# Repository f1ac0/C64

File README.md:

# C64
I bought my fisrt C64. It was listed as "Untested", and of course it was faulty (12v fuse in PSU, 6569 VIC-II that I replaced with a 8565, RAM U10 replaced with a 41256 and 7406 U8 with dead output to IEC port).

While repairing it, I learned about the components inside the C64, their signals and common faults. I bookmarked open-source alternatives and useful expansions : below is a list of the projects I found interesting.

In this repository I share the boards I created or modified for my own needs (for example to use the parts I have in stock, to add features, or because I like my own routing). At the time of writing, some are still untested. 

# Disclaimer and Acknowledgements
This is a hobbyist project, it comes with no warranty and no support. Also remember that the Commodore machines are about 40 years old and may fail because of such hardware expansions.

I publish my work under the CC-BY-NC-SA license, unless stated otherwise. Thanks to everyone who share their knowledge and creations.

# Cartridge
Simple cartridges :
- https://github.com/bwack/Versa64Cart
- https://github.com/SukkoPera/OpenC64Cart
- https://github.com/SukkoPera/OpenC64Cart16K
- https://github.com/SukkoPera/OpenC64KernalCart

Diagnostic :
- https://github.com/svenpetersen1965/Diag64cart
- https://github.com/svenpetersen1965/C64-Diagnostic-Rev.-586220-Harness

Advanced cartridges :
- https://github.com/KimJorgensen/KungFuFlash
- https://github.com/Sgw32/KungFuFlashGD32
- https://github.com/frntc/RAD
- https://github.com/crystalct/MagicDesk2
- https://github.com/msolajic/c64-uni-cart

# CIA

# CPU
- https://github.com/monotech/MOS_CPU_Replacer

# Drive
- https://cbm-pi1541.firebaseapp.com/
- https://github.com/pi1541/Pi1541
- https://github.com/hackup/Pi1541io
- https://github.com/tebl/C64-Pi1541-Module
- https://github.com/Beaupre-Circuit-Design/c64-Pi1541

# Modulator
- https://github.com/c0pperdragon/C64-Video-Enhancement/tree/master/analog_only
- https://github.com/pmandes/C64-RF-Modulator
- https://github.com/tebl/C64-Modulator-Replacement
- https://github.com/mbarszcz-pcb/c64-rf-modulator-replacement

# PLA
- https://github.com/1c3d1v3r/neatPLA
- https://github.com/desaster/c64-dodgypla
- https://www.freepascal.org/~daniel/c64pla/

# RAM

# ROM
- https://github.com/SukkoPera/Open2327RomAdapter
- https://www.hackup.net/2022/05/the-kernal-quattro-a-2364-rom-replacement/

# SID
- http://tolaemon.com/nss/
- https://github.com/jsanpe/SwinsidNeat
- https://github.com/dmantione/swinsid

# Tape
- https://github.com/sweetlilmre/tapuino
- http://sweetlilmre.blogspot.com/2015/03/building-tapuino-r2.html
- https://github.com/sweetlilmre/TapuinoNext

# VIC2
- https://github.com/Jartza/8565_adapter

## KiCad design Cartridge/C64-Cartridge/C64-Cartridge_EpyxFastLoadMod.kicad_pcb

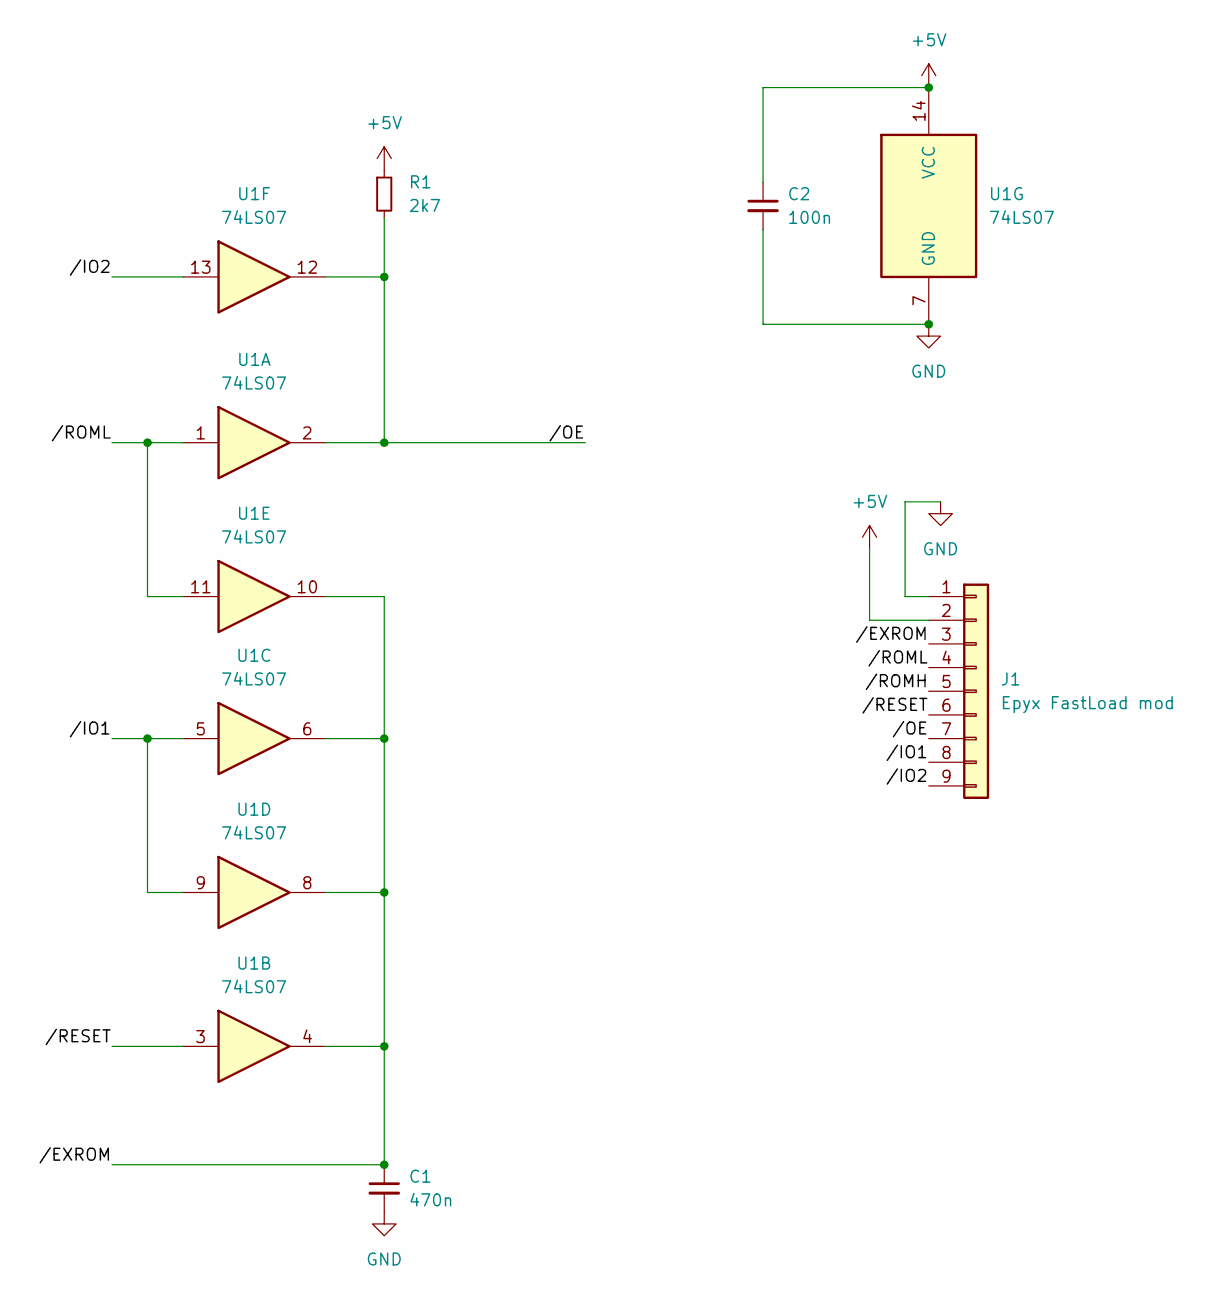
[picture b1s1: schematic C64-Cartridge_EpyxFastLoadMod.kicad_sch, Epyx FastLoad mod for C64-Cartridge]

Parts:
C1: 470n; C_0805_2012Metric
C2: 100n; C_0805_2012Metric
J1: Epyx FastLoad mod; PinHeader_1x09_P1.27mm_Vertical
R1: 2k7; R_0805_2012Metric
U1: 74LS07; SOIC-14_3.9x8.7mm_P1.27mm

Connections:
+5V: C2.1, J1.2, R1.1, U1.14 (VCC)
//EXROM: C1.1, J1.3, U1.4, U1.6, U1.8, U1.10
//IO1: J1.8, U1.5, U1.9
//IO2: J1.9, U1.13
//OE: J1.7, R1.2, U1.2, U1.12
//RESET: J1.6, U1.3
//ROMH: J1.5
//ROML: J1.4, U1.1, U1.11
GND: C1.2, C2.2, J1.1, U1.7 (GND)

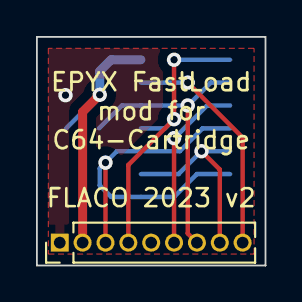
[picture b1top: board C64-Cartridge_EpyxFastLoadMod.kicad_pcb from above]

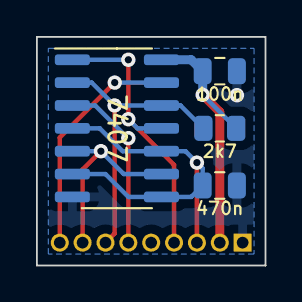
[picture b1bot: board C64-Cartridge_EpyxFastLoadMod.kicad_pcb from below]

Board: 2 copper layers, 12.7 x 12.7 mm, 5 parts (4 on the bottom side), 8 nets.

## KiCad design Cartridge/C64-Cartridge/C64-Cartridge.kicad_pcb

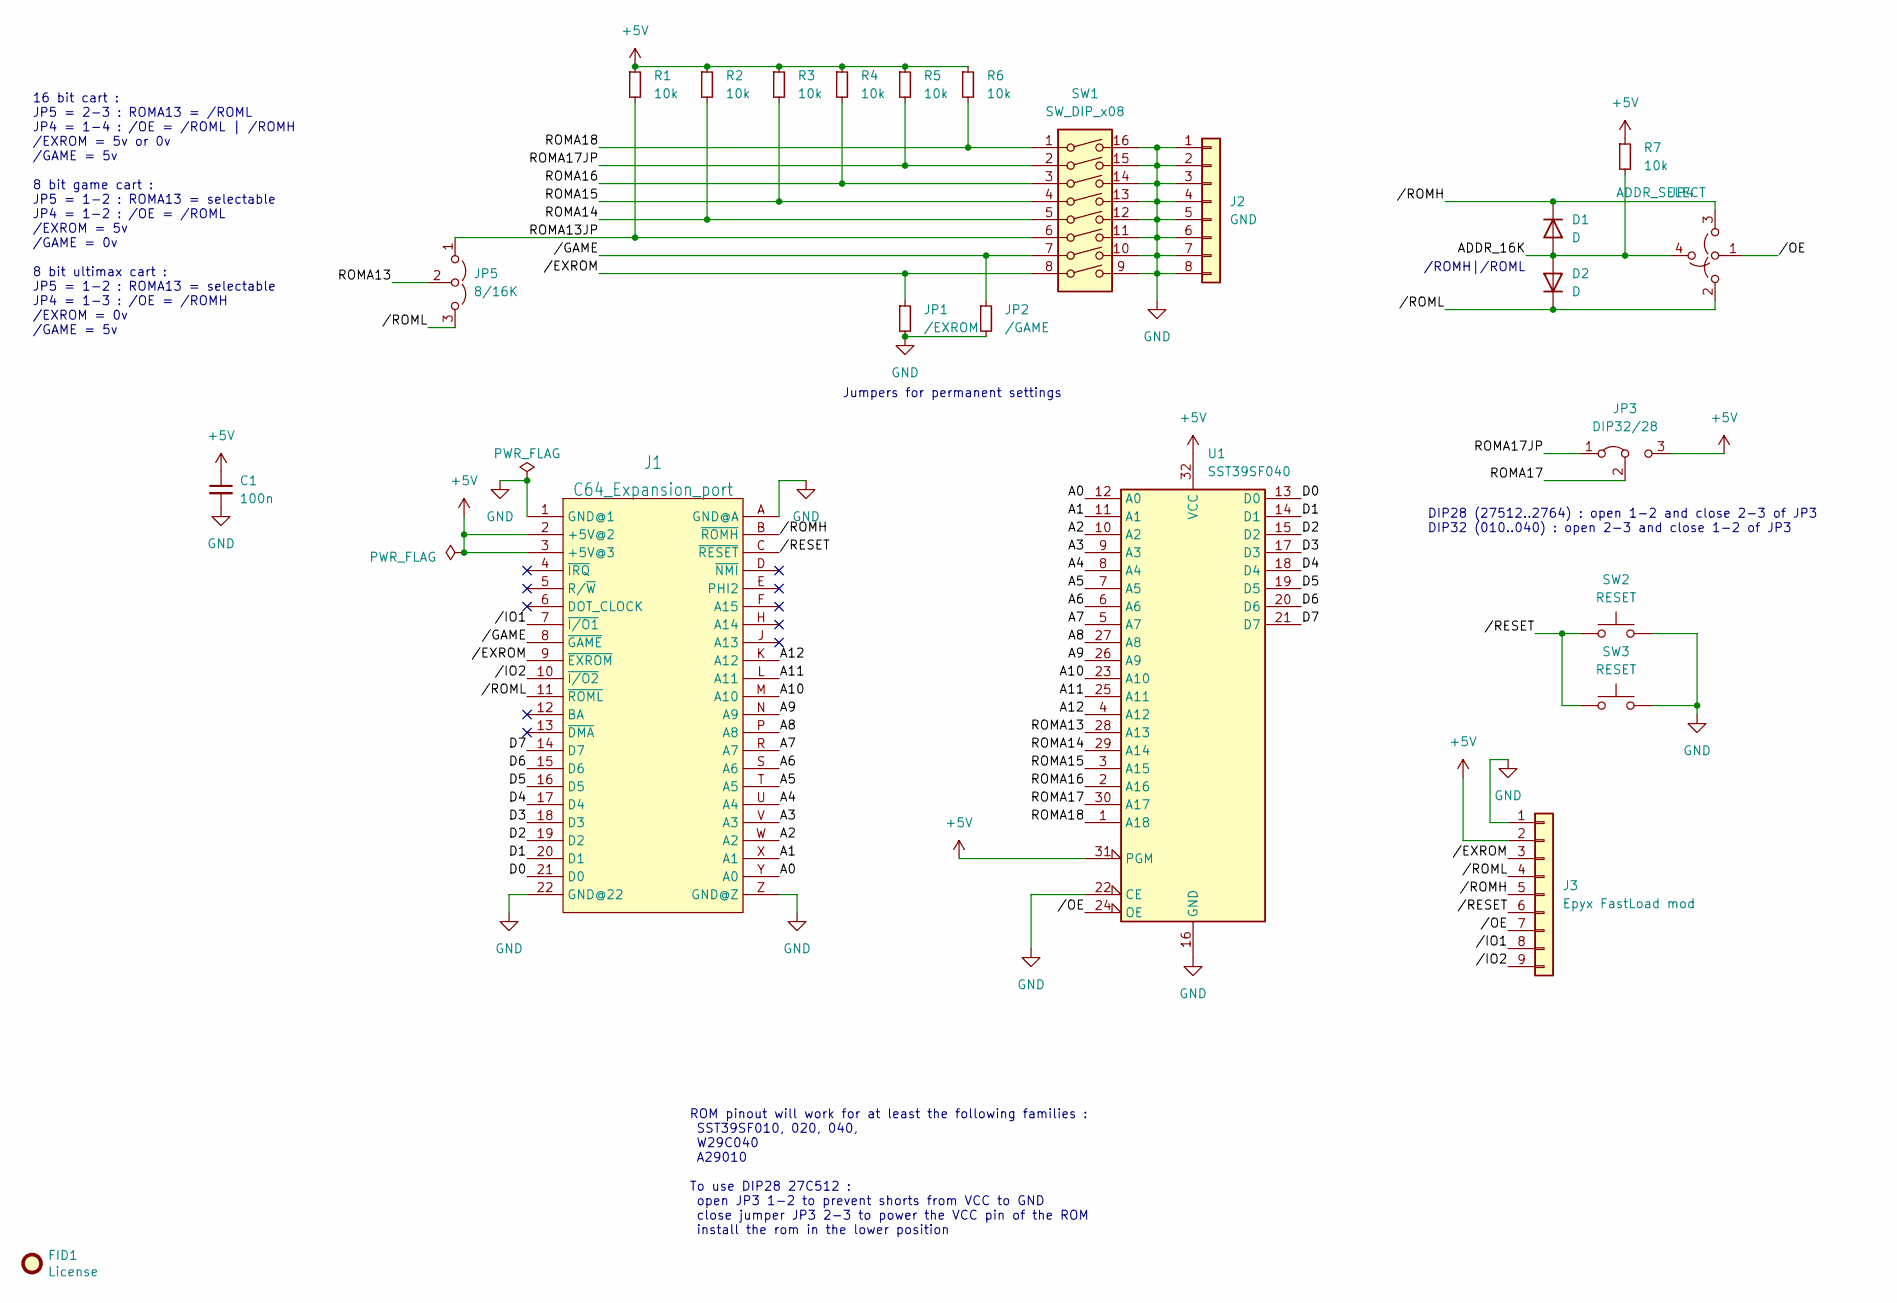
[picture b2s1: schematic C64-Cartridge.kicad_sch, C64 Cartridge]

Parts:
C1: 100n; C_0805_2012Metric
D1, D2: D; D_0805_2012Metric
FID1: License; CC_BY_NC_SA_square_silkscreen
J1: C64_Expansion_port; C64_Expansion_2x22_P2.54mm
J2: GND; PinHeader_1x08_P2.54mm_Vertical
J3: Epyx FastLoad mod; PinHeader_1x09_P1.27mm_Vertical
JP1: /EXROM; SolderJumper-2_P1.3mm_Open_RoundedPad1.0x1.5mm
JP2: /GAME; SolderJumper-2_P1.3mm_Open_RoundedPad1.0x1.5mm
JP3: DIP32/28; SolderJumper-3_P1.3mm_Open_RoundedPad1.0x1.5mm
JP4: ADDR_SELECT; Jumper_4_SPTT_P2.54mm_Vertical
JP5: 8/16K; Jumper_3_SPDT_P2.54mm_Vertical
R1, R2, R3, R4, R5, R6, R7: 10k; R_0805_2012Metric
SW1: SW_DIP_x08; SW_DIP_SPSTx08_Slide_9.78x22.5mm_W7.62mm_P2.54mm
SW2: RESET; SW_SPST_FSMSM
SW3: RESET; SW_PUSH_6mm
U1: SST39SF040; DIP-32_W15.24mm

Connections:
+5V: C1.1, J1.2 (+5V@2), J1.3 (+5V@3), J3.2, JP3.3 (B), R1.1, R2.1, R3.1, R4.1, R5.1, R6.1, R7.1, U1.31 (PGM), U1.32 (VCC)
/A0: J1.Y (A0), U1.12 (A0)
/A1: J1.X (A1), U1.11 (A1)
/A2: J1.W (A2), U1.10 (A2)
/A3: J1.V (A3), U1.9 (A3)
/A4: J1.U (A4), U1.8 (A4)
/A5: J1.T (A5), U1.7 (A5)
/A6: J1.S (A6), U1.6 (A6)
/A7: J1.R (A7), U1.5 (A7)
/A8: J1.P (A8), U1.27 (A8)
/A9: J1.N (A9), U1.26 (A9)
/A10: J1.M (A10), U1.23 (A10)
/A11: J1.L (A11), U1.25 (A11)
/A12: J1.K (A12), U1.4 (A12)
/ADDR_16K: D1.2 (A), D2.2 (A), JP4.4 (D), R7.2
/D0: J1.21 (D0), U1.13 (D0)
/D1: J1.20 (D1), U1.14 (D1)
/D2: J1.19 (D2), U1.15 (D2)
/D3: J1.18 (D3), U1.17 (D3)
/D4: J1.17 (D4), U1.18 (D4)
/D5: J1.16 (D5), U1.19 (D5)
/D6: J1.15 (D6), U1.20 (D6)
/D7: J1.14 (D7), U1.21 (D7)
/ROMA13: JP5.2 (C), U1.28 (A13)
/ROMA13JP: JP5.1 (A), R1.2, SW1.6
/ROMA14: R2.2, SW1.5, U1.29 (A14)
/ROMA15: R3.2, SW1.4, U1.3 (A15)
/ROMA16: R4.2, SW1.3, U1.2 (A16)
/ROMA17: JP3.2 (C), U1.30 (A17)
/ROMA17JP: JP3.1 (A), R5.2, SW1.2
/ROMA18: R6.2, SW1.1, U1.1 (A18)
//EXROM: J1.9 (~EXROM), J3.3, JP1.1, SW1.8
//GAME: J1.8 (~GAME), JP2.1, SW1.7
//IO1: J1.7 (~I/O1), J3.8
//IO2: J1.10 (~I/O2), J3.9
//OE: J3.7, JP4.1 (A), U1.24 (OE)
//RESET: J1.C (~RESET), J3.6, SW2.1, SW3.1
//ROMH: D1.1 (K), J1.B (~ROMH), J3.5, JP4.3 (B)
//ROML: D2.1 (K), J1.11 (~ROML), J3.4, JP4.2 (B), JP5.3 (B)
GND: C1.2, J1.1 (GND@1), J1.22 (GND@22), J1.A (GND@A), J1.Z (GND@Z), J2.1, J2.2, J2.3, J2.4, J2.5, J2.6, J2.7, J2.8, J3.1, JP1.2, JP2.2, SW1.9, SW1.10, SW1.11, SW1.12, SW1.13, SW1.14, SW1.15, SW1.16, SW2.2, SW3.2, U1.16 (GND), U1.22 (CE)

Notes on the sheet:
Jumpers for permanent settings
/ROMH|/ROML
16 bit cart : JP5 = 2-3 : ROMA13 = /ROML JP4 = 1-4 : /OE = /ROML | /ROMH /EXROM = 5v or 0v /GAME = 5v 8 bit game cart : JP5 = 1-2 : ROMA13 = selectable JP4 = 1-2 : /OE = /ROML /EXROM = 5v /GAME = 0v 8 bit ultimax cart : JP5 = 1-2 : ROMA13 = selectable JP4 = 1-3 : /OE = /ROMH /EXROM = 0v /GAME = 5v
ROM pinout will work for at least the following families : SST39SF010, 020, 040, W29C040 A29010 To use DIP28 27C512 : open JP3 1-2 to prevent shorts from VCC to GND close jumper JP3 2-3 to power the VCC pin of the ROM install the rom in the lower position
DIP28 (27512..2764) : open 1-2 and close 2-3 of JP3 DIP32 (010..040) : open 2-3 and close 1-2 of JP3

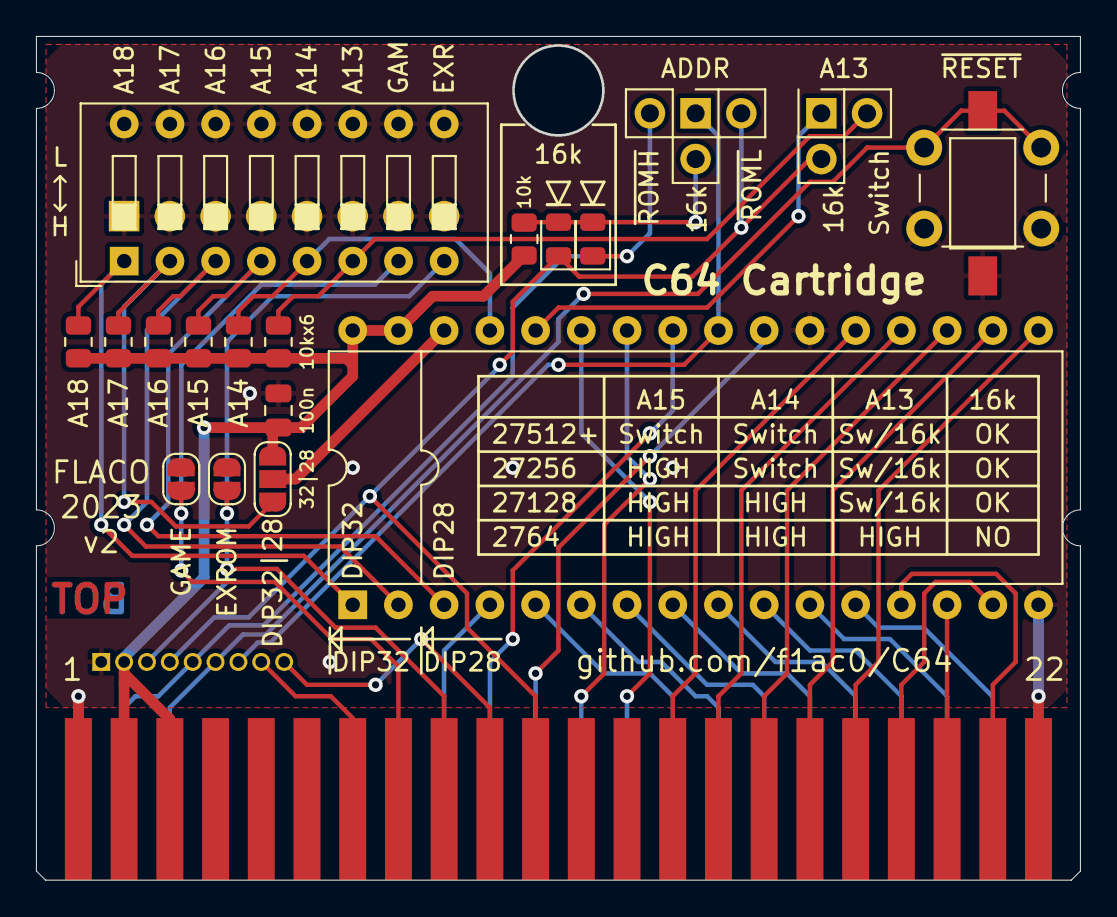
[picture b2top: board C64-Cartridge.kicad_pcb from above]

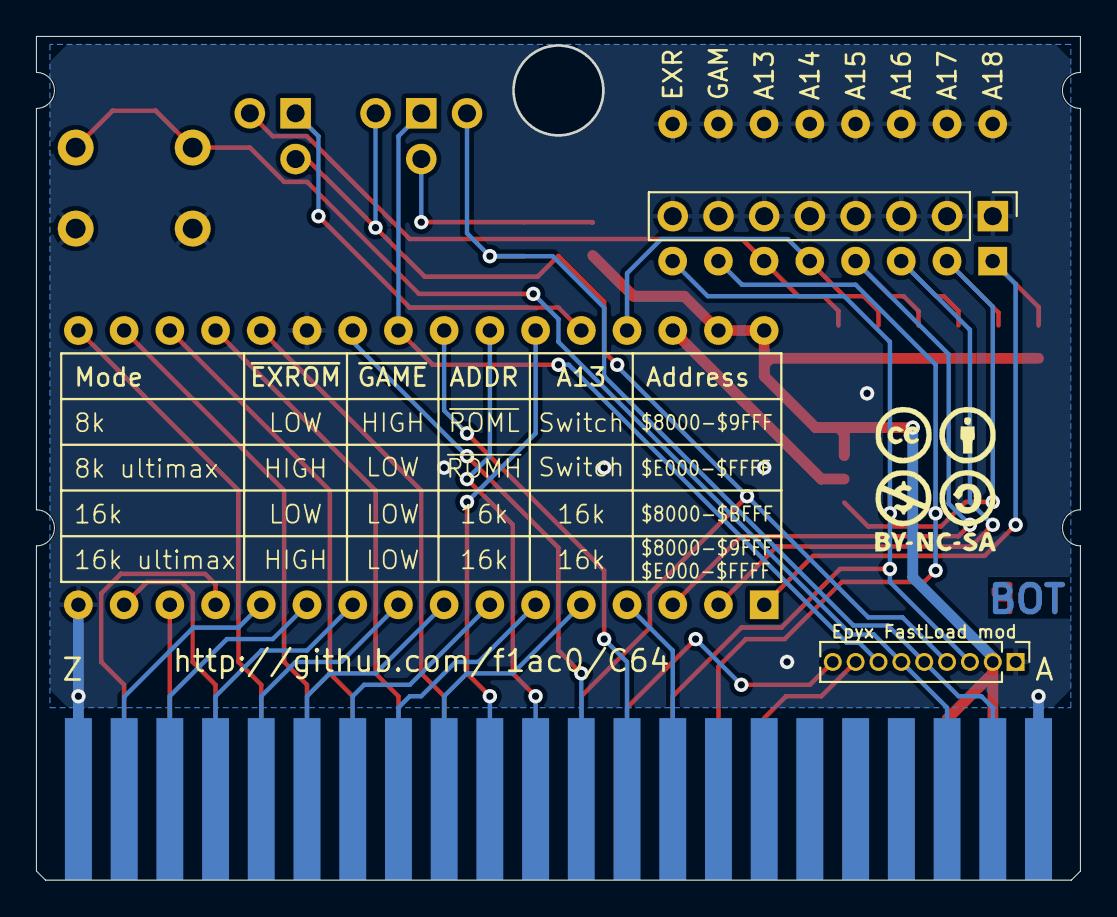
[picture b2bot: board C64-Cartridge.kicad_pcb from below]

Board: 2 copper layers, 57.9 x 46.8 mm, 23 parts (3 on the bottom side), 40 nets.

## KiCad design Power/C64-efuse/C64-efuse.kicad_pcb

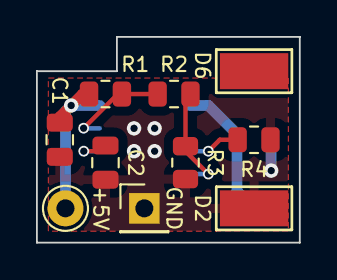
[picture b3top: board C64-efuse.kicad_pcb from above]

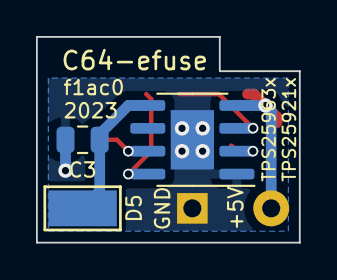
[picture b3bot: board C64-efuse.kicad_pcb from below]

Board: 2 copper layers, 14.6 x 11.4 mm, 13 parts (3 on the bottom side), 7 nets.

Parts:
C1, C3: 0.1-1uF; C_0805_2012Metric
C2: C_dVdt; C_0805_2012Metric
H1: Pin 6 mount; TestPoint_Keystone_5019_Minature
J1: +5V; Pin_D1.0mm_L10.0mm
J2: GND; PinHeader_1x01_P2.54mm_Vertical
J3: Pin 5; TestPoint_Keystone_5019_Minature
J4: Pin 2; TestPoint_Keystone_5019_Minature
R1, R2, R3: R_Small; R_0805_2012Metric
R4: R_ILIM; R_0805_2012Metric
U2: TPS259630; SOIC-8-1EP_3.9x4.9mm_P1.27mm_EP2.41x3.3mm

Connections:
+5F: C3.1, J3.1, U2.5 (OUT)
+5V: C1.1, J1.1, R1.1, U2.4 (VIN)
GND: C1.2, C2.2, C3.2, J2.1, J4.1, R3.2, R4.2, U2.1 (GND), U2.9 (GND)
unnamed: R1.2, R2.1, U2.3 (EN/UVLO)
unnamed: R4.1, U2.7 (ILIM)
unnamed: R2.2, R3.1, U2.8 (OVLO/OVCSEL)
unnamed: C2.1, U2.2 (dV/dT)

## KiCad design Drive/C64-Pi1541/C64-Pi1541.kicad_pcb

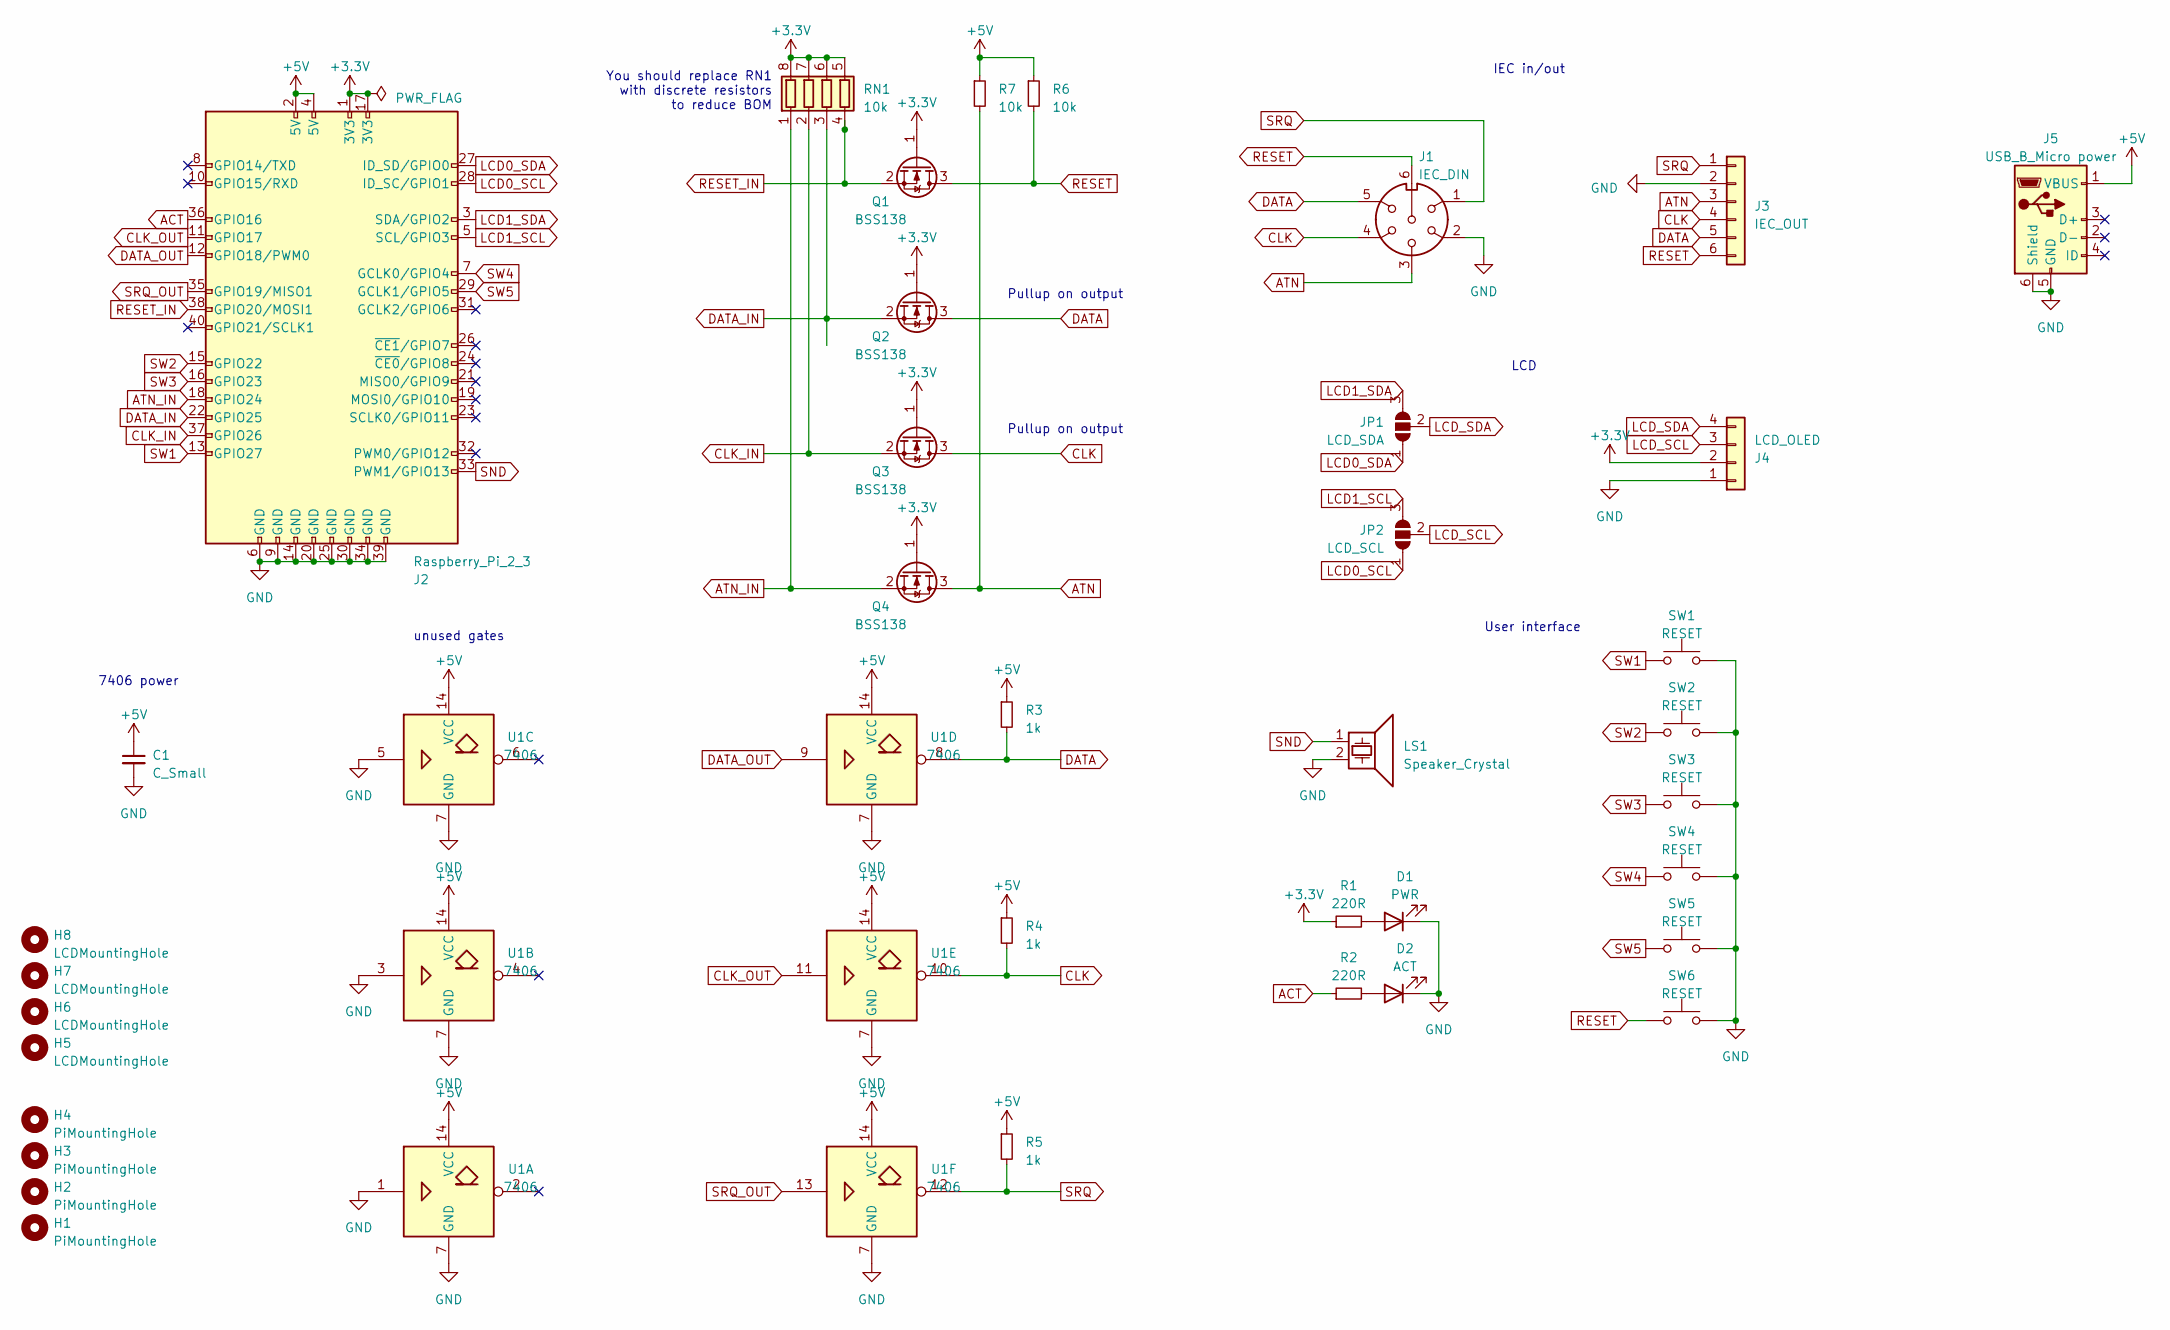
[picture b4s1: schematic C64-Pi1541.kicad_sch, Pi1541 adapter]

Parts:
C1: C_Small; C_0805_2012Metric
D1: PWR; D_0805_2012Metric
D2: ACT; D_0805_2012Metric
H1, H2, H3, H4: PiMountingHole; MountingHole_2.5mm
H5, H6, H7, H8: LCDMountingHole; MountingHole_2.5mm
J1: IEC_DIN; DIN-6-Variable
J2: Raspberry_Pi_2_3; PinSocket_2x20_P2.54mm_Vertical
J3: IEC_OUT; PinHeader_1x06_P2.54mm_Vertical
J4: LCD_OLED; PinSocket_1x04_P2.54mm_Vertical
J5: USB_B_Micro power; USB_Micro-B_Molex-105017-0001
JP1: LCD_SDA; SolderJumper-3_P1.3mm_Open_RoundedPad1.0x1.5mm_NumberLabels
JP2: LCD_SCL; SolderJumper-3_P1.3mm_Open_RoundedPad1.0x1.5mm_NumberLabels
LS1: Speaker_Crystal; PinHeader_1x02_P2.54mm_Vertical
Q1, Q2, Q3, Q4: BSS138; SOT-23
R1, R2: 220R; R_0805_2012Metric
R3, R4, R5: 1k; R_0805_2012Metric
R6, R7: 10k; R_0805_2012Metric
RN1: 10k; R_Array_Convex_4x0603
SW1, SW2, SW3, SW4, SW5, SW6: RESET; SW_Tactile_SPST_Angled_PTS645Vx83-2LFS
U1: 7406; DIP-14_W7.62mm

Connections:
+3.3V: J2.1 (3V3), J2.17 (3V3), J4.2, Q1.1 (G), Q2.1 (G), Q3.1 (G), Q4.1 (G), R1.1, RN1.5 (R4.2), RN1.6 (R3.2), RN1.7 (R2.2), RN1.8 (R1.2)
+5V: C1.1, J2.2 (5V), J2.4 (5V), J5.1 (VBUS), R3.1, R4.1, R5.1, R6.1, R7.1, U1.14 (VCC)
ACT: J2.36 (GPIO16), R2.1
ATN: J1.3, J3.3, Q4.3 (D), R7.2
ATN_IN: J2.18 (GPIO24), Q4.2 (S), RN1.1 (R1.1)
CLK: J1.4, J3.4, Q3.3 (D), R4.2, U1.10
CLK_IN: J2.37 (GPIO26), Q3.2 (S), RN1.2 (R2.1)
CLK_OUT: J2.11 (GPIO17), U1.11
DATA: J1.5, J3.5, Q2.3 (D), R3.2, U1.8
DATA_IN: J2.22 (GPIO25), Q2.2 (S), RN1.3 (R3.1)
DATA_OUT: J2.12 (GPIO18/PWM0), U1.9
GND: C1.2, D1.1 (K), D2.1 (K), J1.2, J2.6 (GND), J2.9 (GND), J2.14 (GND), J2.20 (GND), J2.25 (GND), J2.30 (GND), J2.34 (GND), J2.39 (GND), J3.2, J4.1, J5.5 (GND), J5.6 (Shield), LS1.2, SW1.2, SW2.2, SW3.2, SW4.2, SW5.2, SW6.2, U1.1, U1.3, U1.5, U1.7 (GND)
LCD0_SCL: J2.28 (ID_SC/GPIO1), JP2.1 (A)
LCD0_SDA: J2.27 (ID_SD/GPIO0), JP1.1 (A)
LCD1_SCL: J2.5 (SCL/GPIO3), JP2.3 (B)
LCD1_SDA: J2.3 (SDA/GPIO2), JP1.3 (B)
LCD_SCL: J4.3, JP2.2 (C)
LCD_SDA: J4.4, JP1.2 (C)
unnamed: D1.2 (A), R1.2
unnamed: D2.2 (A), R2.2
RESET: J1.6, J3.6, Q1.3 (D), R6.2, SW6.1
RESET_IN: J2.38 (GPIO20/MOSI1), Q1.2 (S), RN1.4 (R4.1)
SND: J2.33 (PWM1/GPIO13), LS1.1
SRQ: J1.1, J3.1, R5.2, U1.12
SRQ_OUT: J2.35 (GPIO19/MISO1), U1.13
SW1: J2.13 (GPIO27), SW1.1
SW2: J2.15 (GPIO22), SW2.1
SW3: J2.16 (GPIO23), SW3.1
SW4: J2.7 (GCLK0/GPIO4), SW4.1
SW5: J2.29 (GCLK1/GPIO5), SW5.1

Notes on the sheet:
unused gates
User interface
LCD
You should replace RN1 with discrete resistors to reduce BOM
Pullup on output
IEC in/out
7406 power

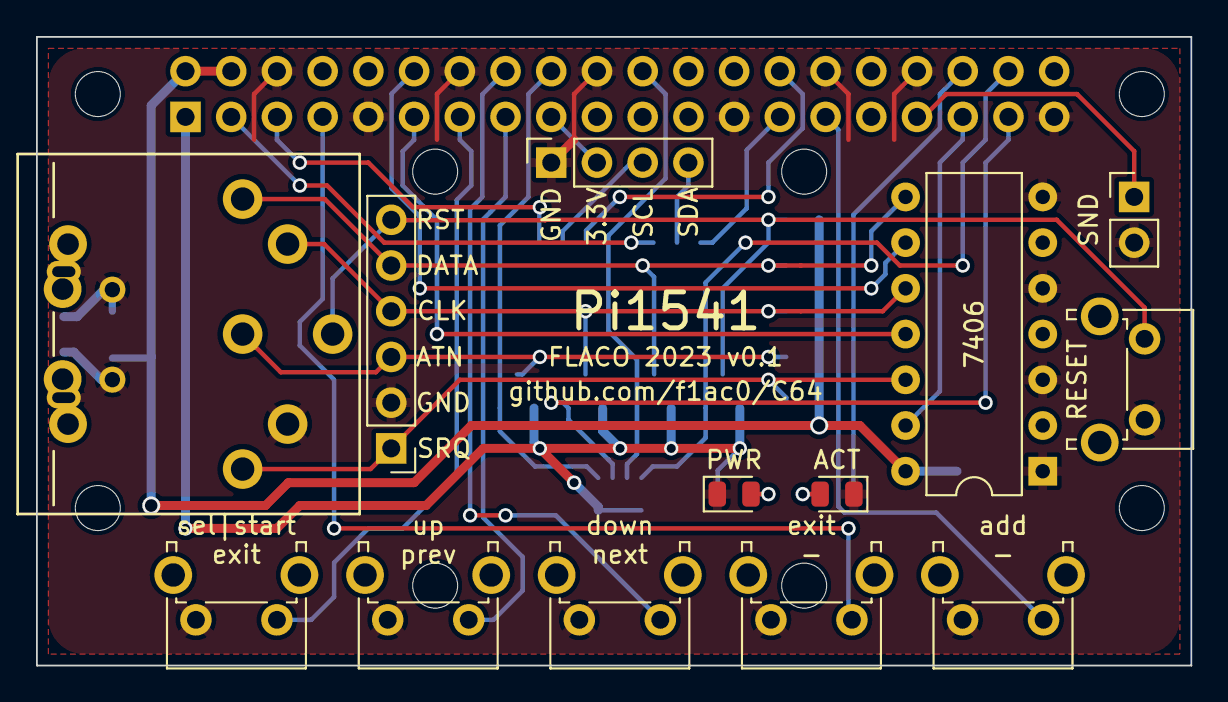
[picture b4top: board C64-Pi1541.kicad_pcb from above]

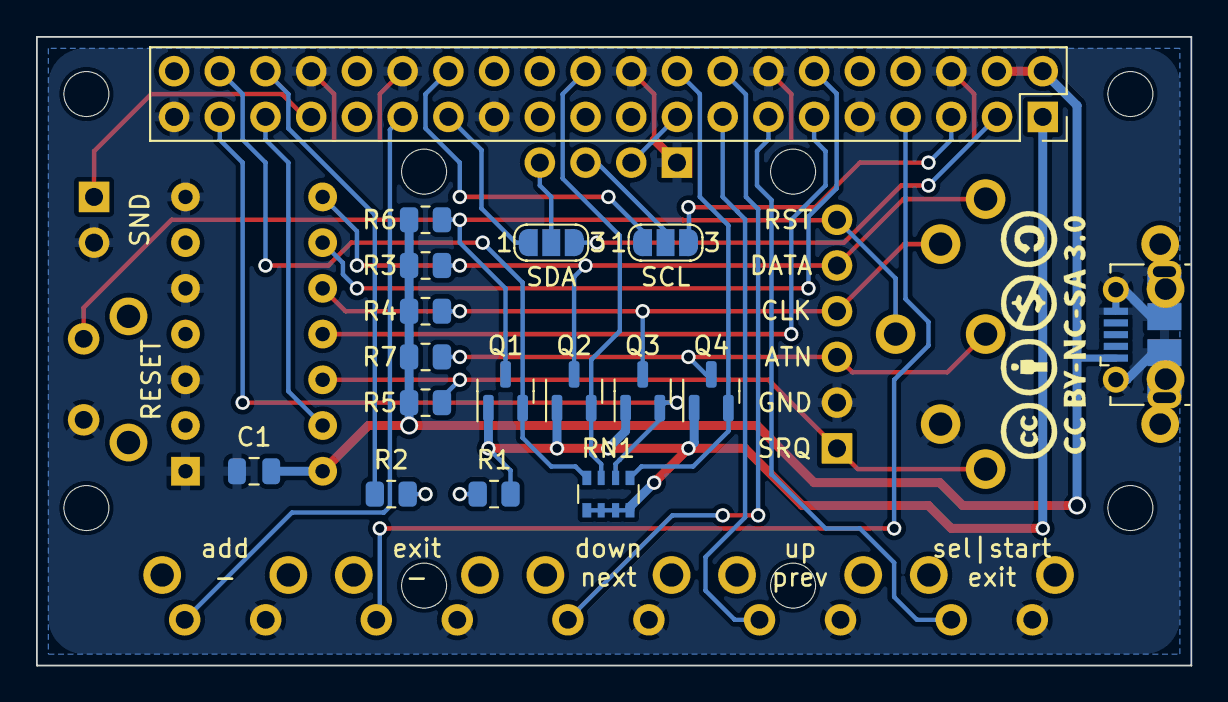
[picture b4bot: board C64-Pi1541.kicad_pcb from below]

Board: 2 copper layers, 64.1 x 34.9 mm, 38 parts (17 on the bottom side), 30 nets.

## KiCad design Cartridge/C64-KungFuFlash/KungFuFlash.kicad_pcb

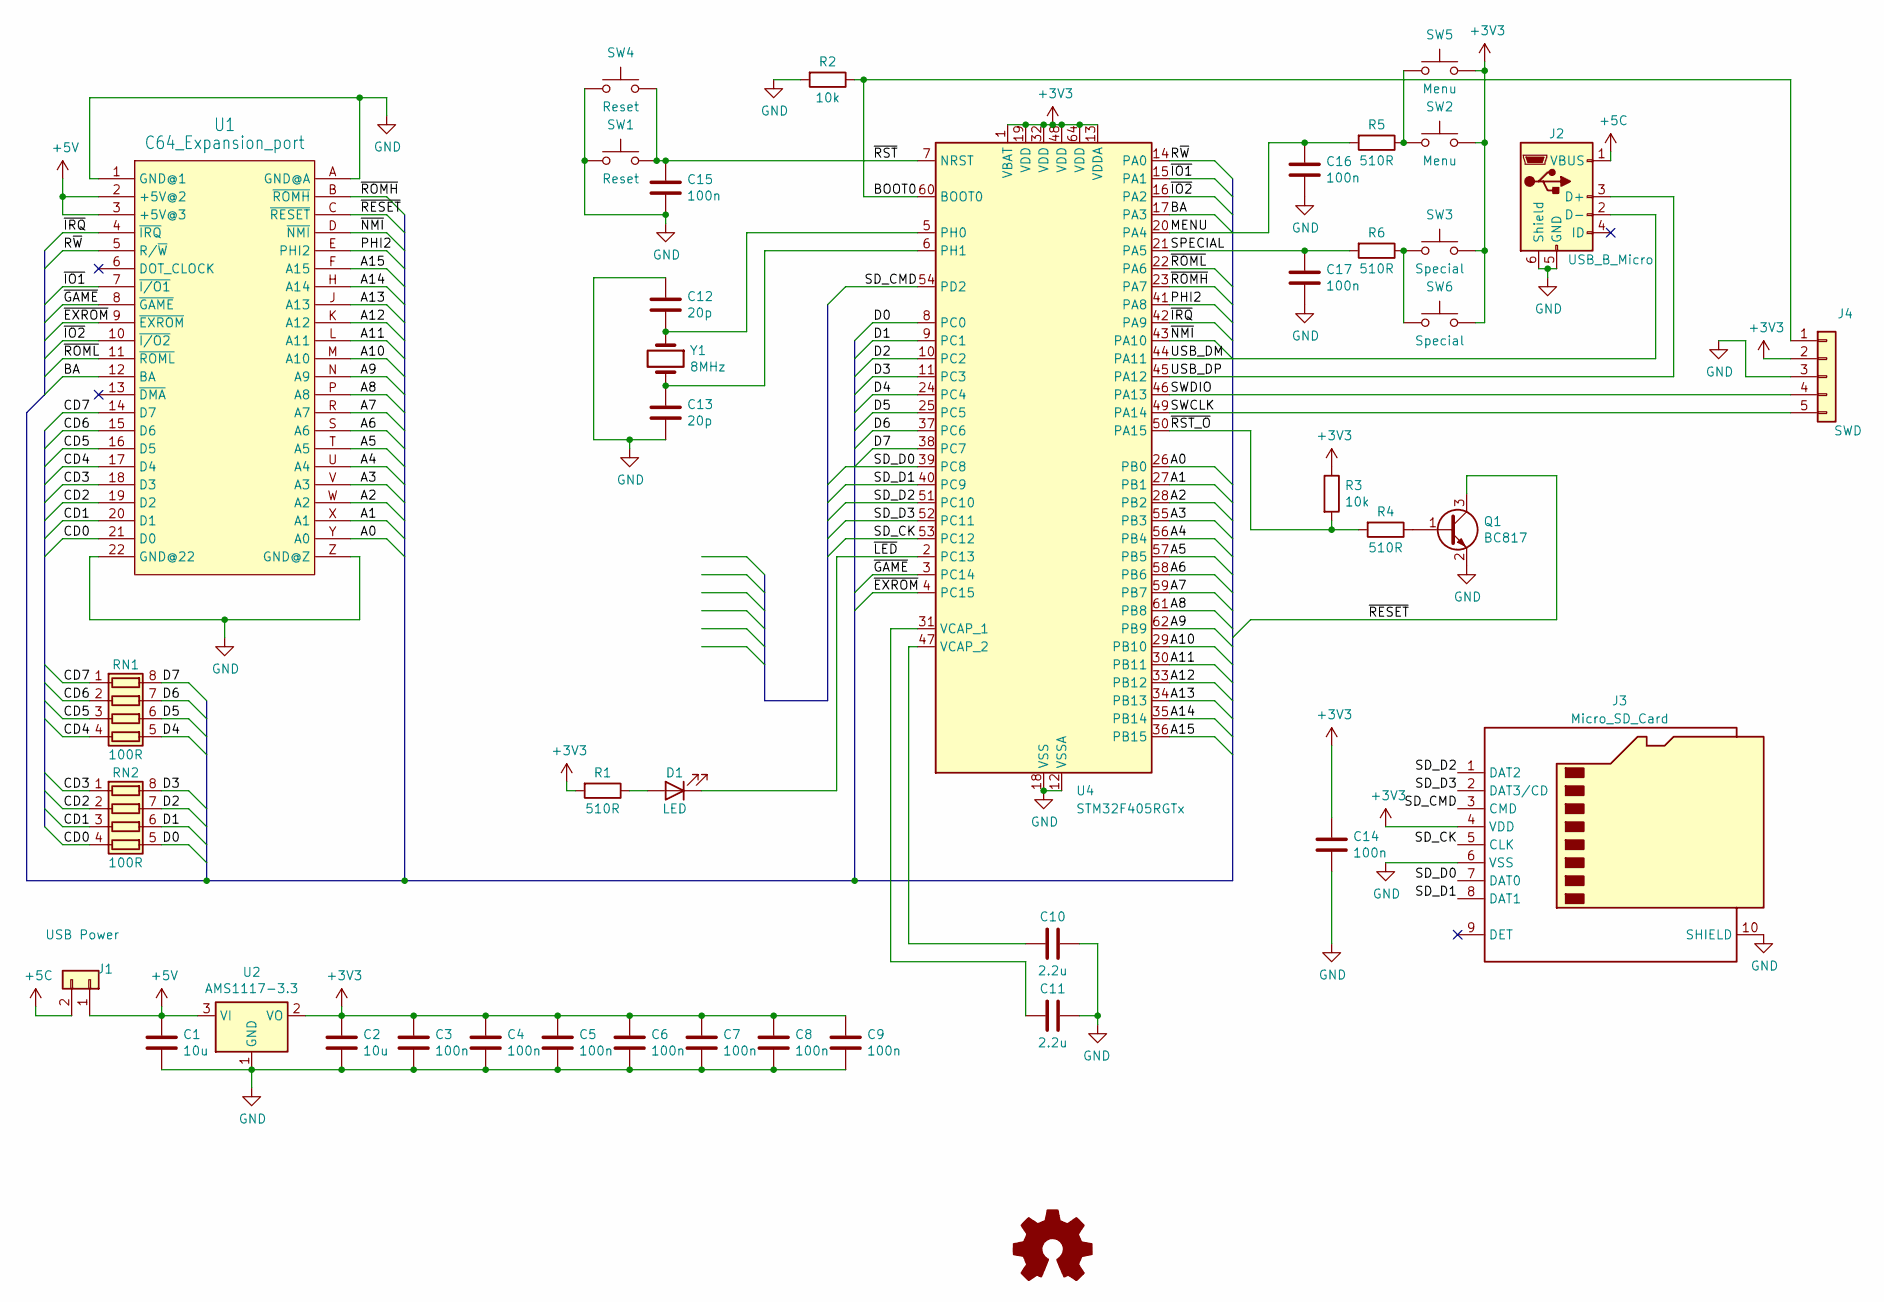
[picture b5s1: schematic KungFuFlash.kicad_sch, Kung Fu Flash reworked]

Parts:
C1, C2: 10u; C_0805_2012Metric_Pad1.18x1.45mm_HandSolder
C3, C4, C5, C6, C7, C8, C9, C14, C15, C16, C17: 100n; C_0805_2012Metric_Pad1.18x1.45mm_HandSolder
C10, C11: 2.2u; C_0805_2012Metric_Pad1.18x1.45mm_HandSolder
C12, C13: 20p; C_0805_2012Metric_Pad1.18x1.45mm_HandSolder
D1: LED; LED_0805_2012Metric_Pad1.15x1.40mm_HandSolder
J1: USB Power; PinHeader_1x02_P2.54mm_Vertical
J2: USB_B_Micro; USB_Micro-B_Molex-105017-0001
J3: Micro_SD_Card; TFP09-2-12B_larger_pad
J4: SWD; PinHeader_1x05_P2.54mm_Vertical
Q1: BC817; SOT-23
R1, R4, R5, R6: 510R; R_0805_2012Metric_Pad1.20x1.40mm_HandSolder
R2, R3: 10k; R_0805_2012Metric_Pad1.20x1.40mm_HandSolder
RN1, RN2: 100R; R_Array_Convex_4x0603
SW1: Reset; SW_PUSH_6mm_H8mm
SW2: Menu; SW_PUSH_6mm_H8mm
SW3: Special; SW_PUSH_6mm_H8mm
SW4: Reset; SW_SPST_CK_RS282G05A3
SW5: Menu; SW_SPST_CK_RS282G05A3
SW6: Special; SW_SPST_CK_RS282G05A3
U1: C64_Expansion_port; C64_Expansion_2x22_P2.54mm
U2: AMS1117-3.3; SOT-223-3_TabPin2
U4: STM32F405RGTx; LQFP-64_10x10mm_P0.5mm
Y1: 8MHz; Crystal_HC49-U_Vertical

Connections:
+3V3: C2.1, C3.1, C4.1, C5.1, C6.1, C7.1, C8.1, C9.1, C14.1, J3.4 (VDD), J4.2, R1.2, R3.1, SW2.1, SW3.1, SW5.1, SW6.1, U2.2 (VO), U4.1 (VBAT), U4.13 (VDDA), U4.19 (VDD), U4.32 (VDD), U4.48 (VDD), U4.64 (VDD)
+5C: J1.2, J2.1 (VBUS)
+5V: C1.1, J1.1, U1.2 (+5V@2), U1.3 (+5V@3), U2.3 (VI)
/A0: U1.Y (A0), U4.26 (PB0)
/A1: U1.X (A1), U4.27 (PB1)
/A2: U1.W (A2), U4.28 (PB2)
/A3: U1.V (A3), U4.55 (PB3)
/A4: U1.U (A4), U4.56 (PB4)
/A5: U1.T (A5), U4.57 (PB5)
/A6: U1.S (A6), U4.58 (PB6)
/A7: U1.R (A7), U4.59 (PB7)
/A8: U1.P (A8), U4.61 (PB8)
/A9: U1.N (A9), U4.62 (PB9)
/A10: U1.M (A10), U4.29 (PB10)
/A11: U1.L (A11), U4.30 (PB11)
/A12: U1.K (A12), U4.33 (PB12)
/A13: U1.J (A13), U4.34 (PB13)
/A14: U1.H (A14), U4.35 (PB14)
/A15: U1.F (A15), U4.36 (PB15)
/BA: U1.12 (BA), U4.17 (PA3)
/BOOT0: J4.1, R2.1, U4.60 (BOOT0)
/CD0: RN2.4 (R4.1), U1.21 (D0)
/CD1: RN2.3 (R3.1), U1.20 (D1)
/CD2: RN2.2 (R2.1), U1.19 (D2)
/CD3: RN2.1 (R1.1), U1.18 (D3)
/CD4: RN1.4 (R4.1), U1.17 (D4)
/CD5: RN1.3 (R3.1), U1.16 (D5)
/CD6: RN1.2 (R2.1), U1.15 (D6)
/CD7: RN1.1 (R1.1), U1.14 (D7)
/D0: RN2.5 (R4.2), U4.8 (PC0)
/D1: RN2.6 (R3.2), U4.9 (PC1)
/D2: RN2.7 (R2.2), U4.10 (PC2)
/D3: RN2.8 (R1.2), U4.11 (PC3)
/D4: RN1.5 (R4.2), U4.24 (PC4)
/D5: RN1.6 (R3.2), U4.25 (PC5)
/D6: RN1.7 (R2.2), U4.37 (PC6)
/D7: RN1.8 (R1.2), U4.38 (PC7)
/MENU: C16.1, R5.2, U4.20 (PA4)
/PHI2: U1.E (PHI2), U4.41 (PA8)
/R~W: U1.5 (R/~W), U4.14 (PA0)
/SD_CK: J3.5 (CLK), U4.53 (PC12)
/SD_CMD: J3.3 (CMD), U4.54 (PD2)
/SD_D0: J3.7 (DAT0), U4.39 (PC8)
/SD_D1: J3.8 (DAT1), U4.40 (PC9)
/SD_D2: J3.1 (DAT2), U4.51 (PC10)
/SD_D3: J3.2 (DAT3/CD), U4.52 (PC11)
/SPECIAL: C17.1, R6.2, U4.21 (PA5)
/SWCLK: J4.5, U4.49 (PA14)
/SWDIO: J4.4, U4.46 (PA13)
/USB_DM: J2.2 (D-), U4.44 (PA11)
/USB_DP: J2.3 (D+), U4.45 (PA12)
/~EXROM: U1.9 (~EXROM), U4.4 (PC15)
/~GAME: U1.8 (~GAME), U4.3 (PC14)
/~IO1: U1.7 (~I/O1), U4.15 (PA1)
/~IO2: U1.10 (~I/O2), U4.16 (PA2)
/~IRQ: U1.4 (~IRQ), U4.42 (PA9)
/~LED: D1.1 (K), U4.2 (PC13)
/~NMI: U1.D (~NMI), U4.43 (PA10)
/~RESET: Q1.3 (C), U1.C (~RESET)
/~ROMH: U1.B (~ROMH), U4.23 (PA7)
/~ROML: U1.11 (~ROML), U4.22 (PA6)
/~RST_O: R3.2, R4.2, U4.50 (PA15)
/~RST: C15.1, SW1.2, SW4.2, U4.7 (NRST)
GND: C1.2, C2.2, C3.2, C4.2, C5.2, C6.2, C7.2, C8.2, C9.2, C10.2, C11.1, C12.1, C13.2, C14.2, C15.2, C16.2, C17.2, J2.5 (GND), J2.6 (Shield), J3.6 (VSS), J3.10 (SHIELD), J4.3, Q1.2 (E), R2.2, SW1.1, SW4.1, U1.1 (GND@1), U1.22 (GND@22), U1.A (GND@A), U1.Z (GND@Z), U2.1 (GND), U4.12 (VSSA), U4.18 (VSS), U4.63 (VSS)
unnamed: D1.2 (A), R1.1
unnamed: Q1.1 (B), R4.1
unnamed: R5.1, SW2.2, SW5.2
unnamed: R6.1, SW3.2, SW6.2
unnamed: C12.2, U4.5 (PH0), Y1.1
unnamed: C13.1, U4.6 (PH1), Y1.2
unnamed: C11.2, U4.31 (VCAP_1)
unnamed: C10.1, U4.47 (VCAP_2)

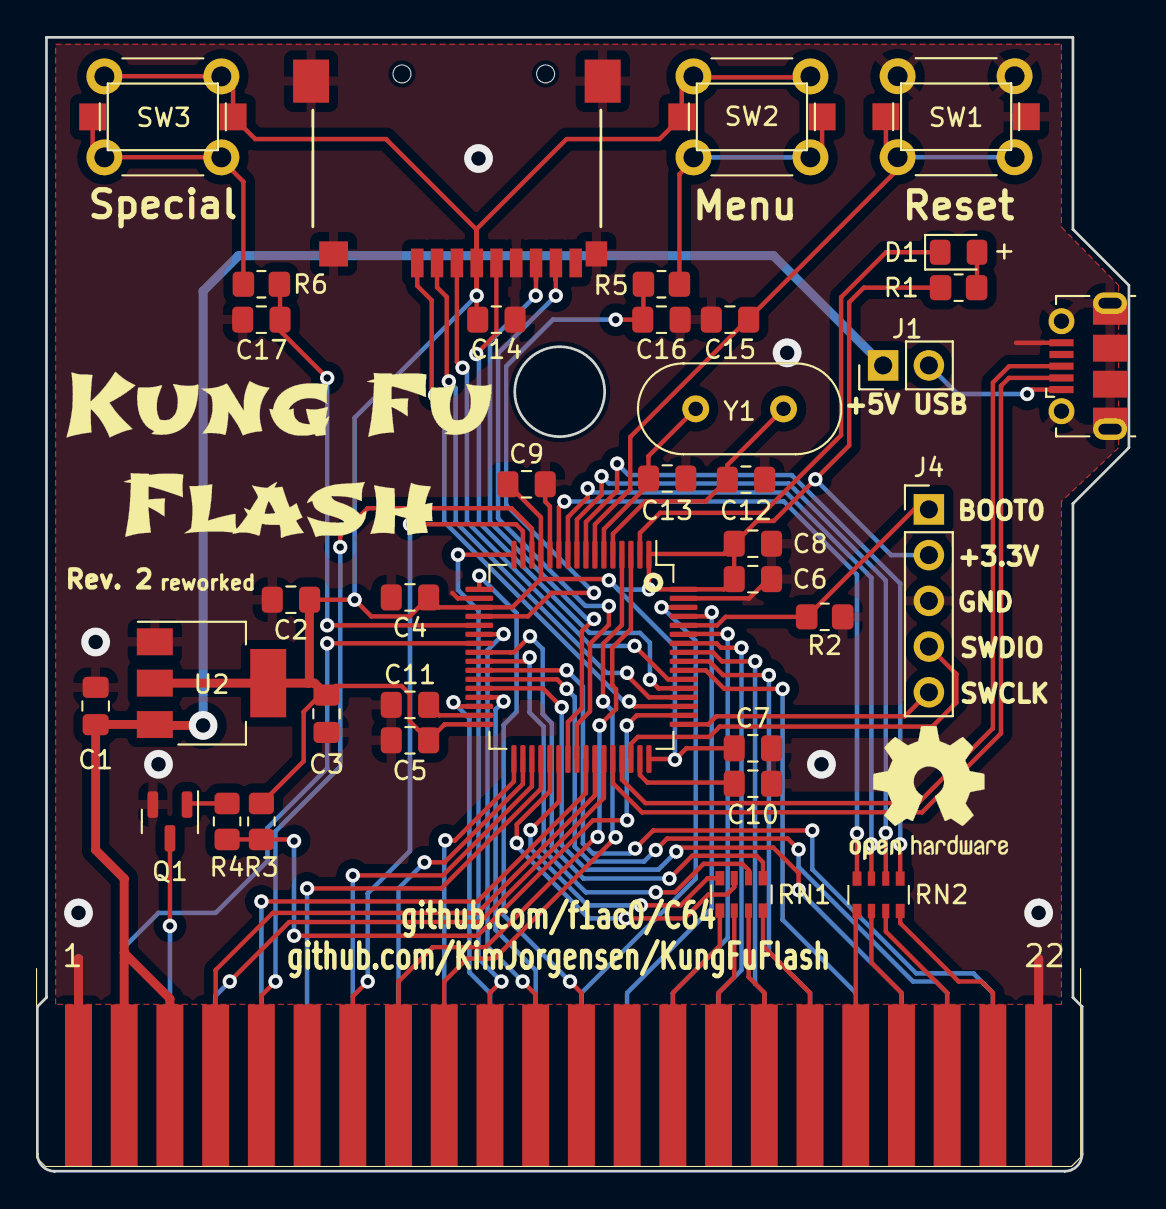
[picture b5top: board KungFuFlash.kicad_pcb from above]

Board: 2 copper layers, 60.6 x 63.0 mm, 41 parts (0 on the bottom side), 72 nets.

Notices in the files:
Cartridge/C64-KungFuFlash/KungFuFlash.kicad_pcb:
open hardware license
RAM/C64-RAM-xx4256to4164/C64-RAM-xx4256to4164.kicad_pcb:
CC-BY-NC-SA 4.0
